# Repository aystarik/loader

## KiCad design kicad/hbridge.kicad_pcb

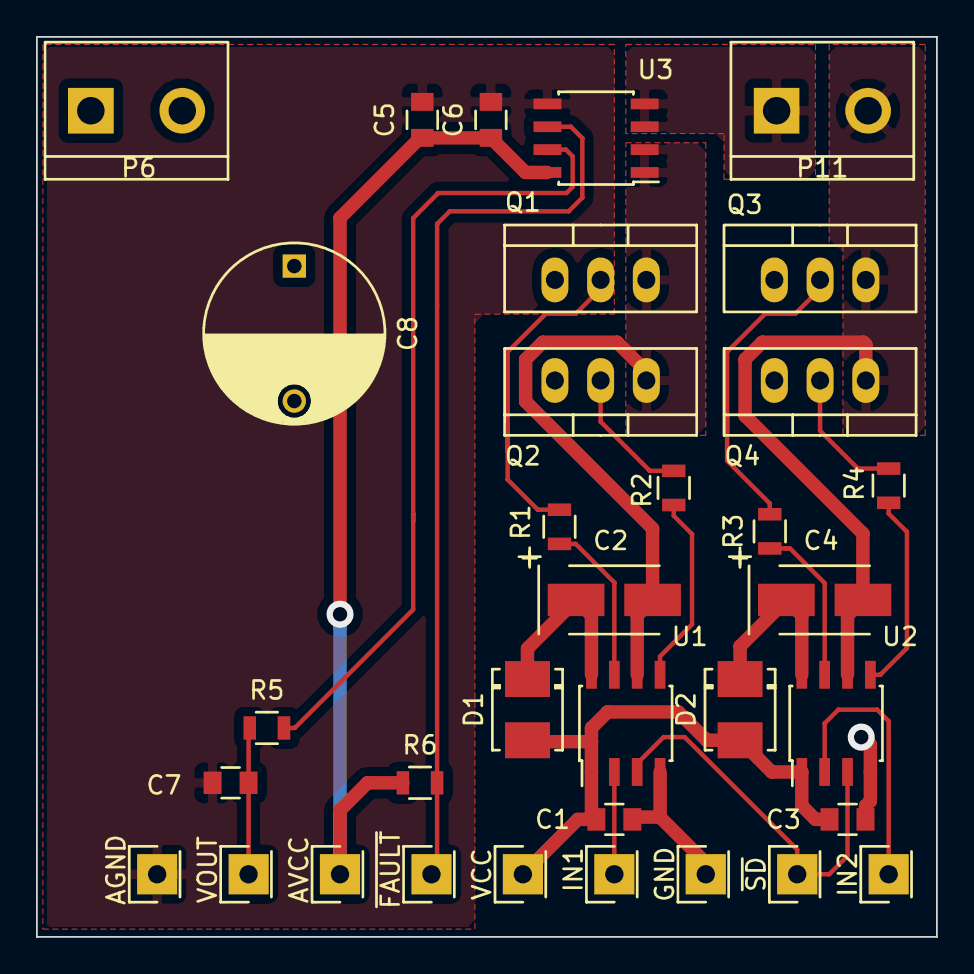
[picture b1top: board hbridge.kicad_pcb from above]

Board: 2 copper layers, 50.0 x 50.0 mm, 35 parts (1 on the bottom side), 23 nets.

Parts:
C1, C3, C5, C6, C7, C9: C; C_0805
C2, C4: C; TantalC_SizeB_EIA-3528_HandSoldering
C8: CP; C_Radial_D10_L20_P7.5
D1, D2: D_Schottky; Diode-DO-214BA
P1: VCC; Socket_Strip_Straight_1x01
P2: IN1; Socket_Strip_Straight_1x01
P3: ~SD; Socket_Strip_Straight_1x01
P4: GND; Socket_Strip_Straight_1x01
P5: IN2; Socket_Strip_Straight_1x01
P6: POWER; bornier2
P7: AVCC; Socket_Strip_Straight_1x01
P8: AGND; Socket_Strip_Straight_1x01
P9: ~FAULT; Socket_Strip_Straight_1x01
P10: VOUT; Socket_Strip_Straight_1x01
P11: OUT; bornier2
Q1, Q2, Q3, Q4: Q_NMOS_DGS; TO-220_Neutral123_Vertical
R1, R2, R3, R4, R5, R6: R; R_0805
U1, U2: IRS2004; SOIC-8_3.9x4.9mm_Pitch1.27mm
U3: ACS711; SOIC-8_3.9x4.9mm_Pitch1.27mm

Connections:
/Current Sensor/AVCC: C5.1, C6.1, P7.1, R6.1, U3.8
/Current Sensor/IP+: C2.2, Q1.3, Q2.1, U1.6, U3.1, U3.2
/Current Sensor/IP-: P11.1, U3.3, U3.4
/Current Sensor/VOUT: C7.1, P10.1, R5.1
/Current Sensor/~FAULT: P9.1, R6.2, U3.6
/Half Bridge/GND: C1.2, C3.2, C8.2, C9.2, P4.1, P6.1, Q2.3, Q4.3, U1.4, U2.4
/Half Bridge/IN: P2.1, P5.1, U1.2, U2.2
/Half Bridge/OUT: C4.2, P11.2, Q3.3, Q4.1, U2.6
/Half Bridge/VCC: C1.1, C3.1, D1.1, D2.1, P1.1, U1.1, U2.1
/Half Bridge/VPP: C8.1, C9.1, P6.2, Q1.1, Q3.1
/Half Bridge/~SD: P3.1, U1.3, U2.3
GNDA: C5.2, C6.2, C7.2, P8.1, U3.5
unnamed: C2.1, D1.2, U1.8
unnamed: C4.1, D2.2, U2.8
unnamed: Q1.2, R1.1
unnamed: Q2.2, R2.1
unnamed: Q3.2, R3.1
unnamed: Q4.2, R4.1
unnamed: R1.2, U1.7
unnamed: R2.2, U1.5
unnamed: R3.2, U2.7
unnamed: R4.2, U2.5
unnamed: R5.2, U3.7

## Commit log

2014-09-05 timing research
2014-09-05 add loader data
2014-09-26 add multithread test
2014-11-28 Add HSM example
2014-12-19 Initial HUD commit
2014-12-22 Add key events
2015-03-17 add hbridge initial schematics
2015-03-20 board step
2015-03-23 add library
2015-04-03 wip #1
2015-04-06 initial place & route
2015-04-07 PCB good
2015-04-13 add big cap for vpp
